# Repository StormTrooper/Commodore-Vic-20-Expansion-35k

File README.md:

# Commodore Vic-20 Expansion 35k

KiCAD schematic for Commodore Vic-20 35k memory expansion

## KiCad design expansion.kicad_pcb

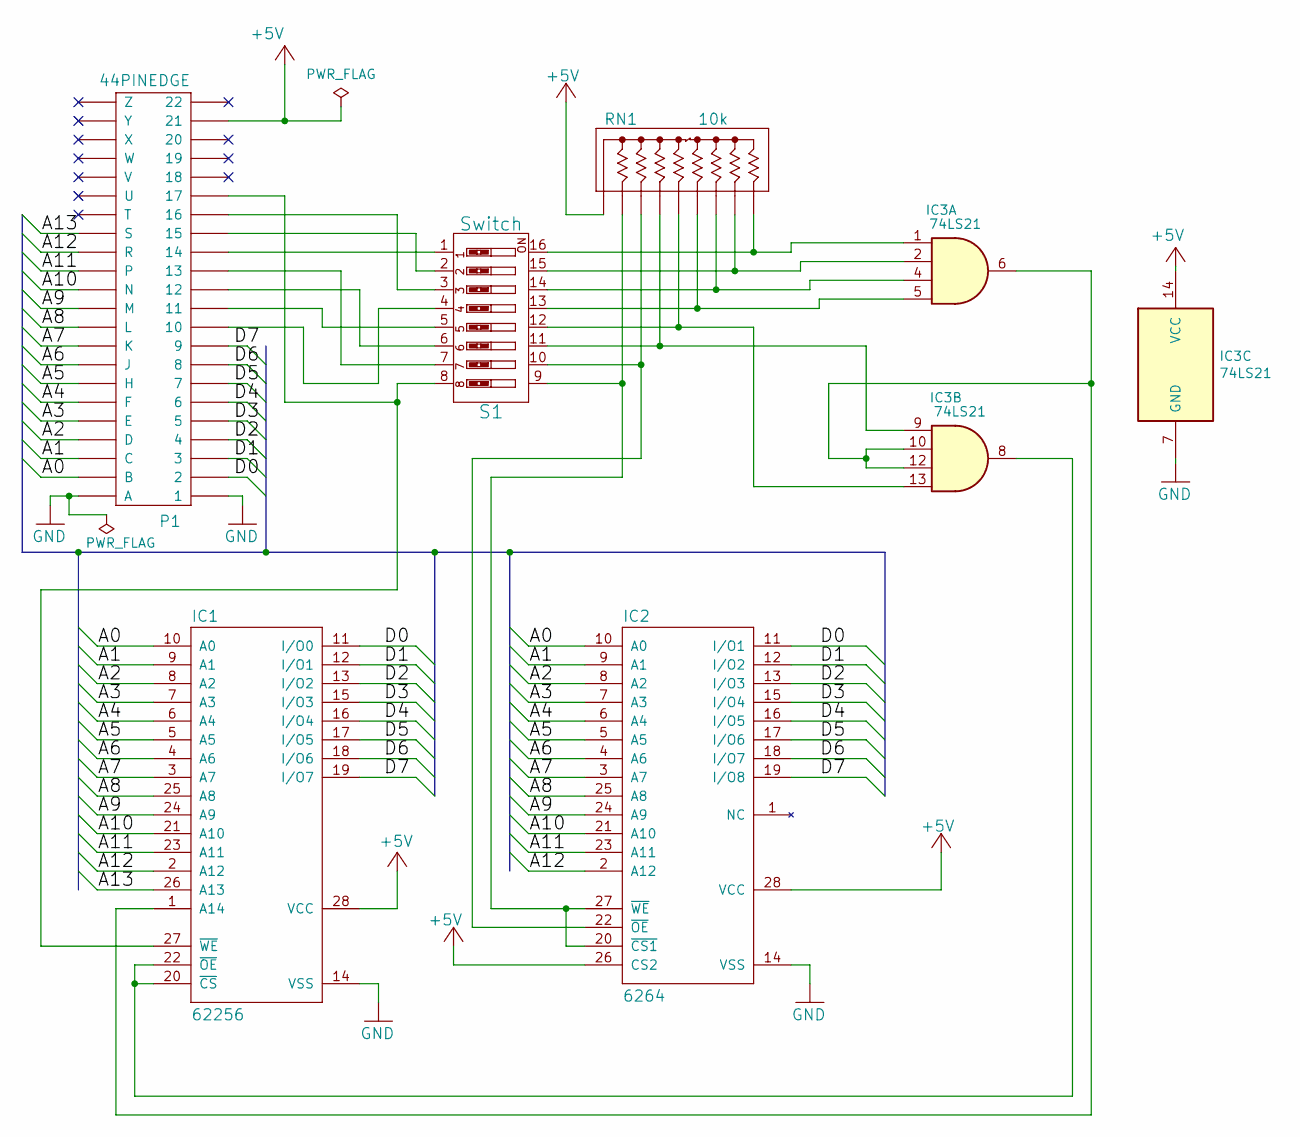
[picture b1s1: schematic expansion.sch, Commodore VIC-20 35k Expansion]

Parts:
IC1: 62256; DIP-28_W15.24mm_LongPads
IC2: 6264; DIP-28_W15.24mm_LongPads
IC3: 74LS21; DIP-14_W7.62mm_LongPads
P1: 44PINEDGE
RN1: 10k; R_Array_SIP9
S1: Switch; SW_DIP_SPSTx08_Slide_9.78x22.5mm_W7.62mm_P2.54mm

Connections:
+5V: IC1.28 (VCC), IC2.26 (CS2), IC2.28 (VCC), IC3.14 (VCC), P1.21, RN1.1
/A0: IC1.10 (A0), IC2.10 (A0), P1.B
/A1: IC1.9 (A1), IC2.9 (A1), P1.C
/A2: IC1.8 (A2), IC2.8 (A2), P1.D
/A3: IC1.7 (A3), IC2.7 (A3), P1.E
/A4: IC1.6 (A4), IC2.6 (A4), P1.F
/A5: IC1.5 (A5), IC2.5 (A5), P1.H
/A6: IC1.4 (A6), IC2.4 (A6), P1.J
/A7: IC1.3 (A7), IC2.3 (A7), P1.K
/A8: IC1.25 (A8), IC2.25 (A8), P1.L
/A9: IC1.24 (A9), IC2.24 (A9), P1.M
/A10: IC1.21 (A10), IC2.21 (A10), P1.N
/A11: IC1.23 (A11), IC2.23 (A11), P1.P
/A12: IC1.2 (A12), IC2.2 (A12), P1.R
/A13: IC1.26 (A13), P1.S
/D0: IC1.11 (I/O0), IC2.11 (I/O1), P1.2
/D1: IC1.12 (I/O1), IC2.12 (I/O2), P1.3
/D2: IC1.13 (I/O2), IC2.13 (I/O3), P1.4
/D3: IC1.15 (I/O3), IC2.15 (I/O4), P1.5
/D4: IC1.16 (I/O4), IC2.16 (I/O5), P1.6
/D5: IC1.17 (I/O5), IC2.17 (I/O6), P1.7
/D6: IC1.18 (I/O6), IC2.18 (I/O7), P1.8
/D7: IC1.19 (I/O7), IC2.19 (I/O8), P1.9
GND: IC1.14 (VSS), IC2.14 (VSS), IC3.7 (GND), P1.1, P1.A
unnamed: IC1.1 (A14), IC3.6, IC3.10, IC3.12
unnamed: IC1.20 (~CS), IC1.22 (~OE), IC3.8
unnamed: IC1.27 (~WE), P1.17, S1.8
unnamed: IC2.20 (~CS1), IC2.27 (~WE), RN1.2, S1.9
unnamed: IC2.22 (~OE), RN1.3, S1.10
unnamed: IC3.1, RN1.9, S1.16
unnamed: IC3.2, RN1.8, S1.15
unnamed: IC3.4, RN1.7, S1.14
unnamed: IC3.5, RN1.6, S1.13
unnamed: IC3.9, RN1.4, S1.11
unnamed: IC3.13, RN1.5, S1.12
unnamed: P1.10, S1.4
unnamed: P1.11, S1.5
unnamed: P1.12, S1.6
unnamed: P1.13, S1.7
unnamed: P1.14, S1.1
unnamed: P1.15, S1.2
unnamed: P1.16, S1.3

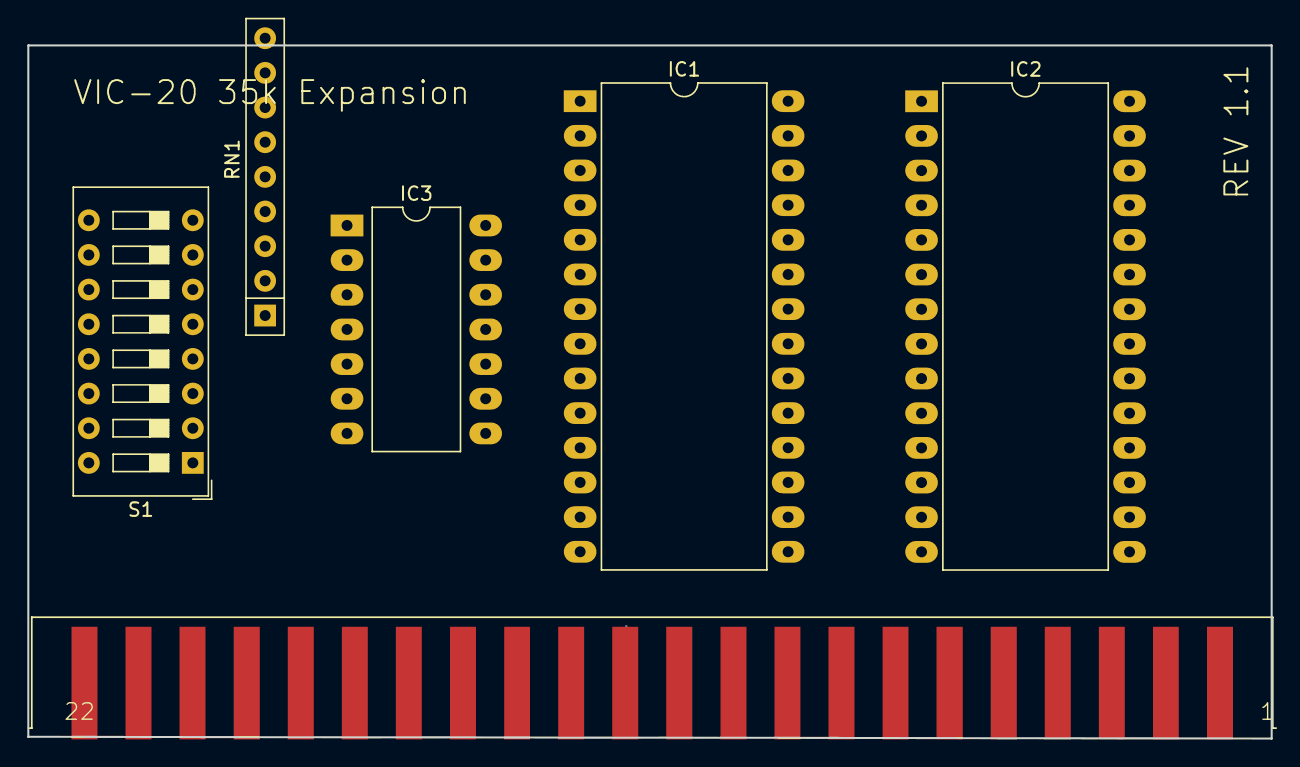
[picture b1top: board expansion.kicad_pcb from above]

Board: 2 copper layers, 91.1 x 50.8 mm, 6 parts (0 on the bottom side), 42 nets.

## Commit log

2019-08-23 Add Readme
